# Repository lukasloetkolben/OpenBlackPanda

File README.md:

# Open Source BlackPanda for Openpilot
__This project has moved, a current version can be found here: [OpenpilotHardware](https://github.com/lukasloetkolben/OpenpilotHardware)__

The device has been tested and works so far without problems.

If you have any questions contact me on Discord: loetkolben#2962

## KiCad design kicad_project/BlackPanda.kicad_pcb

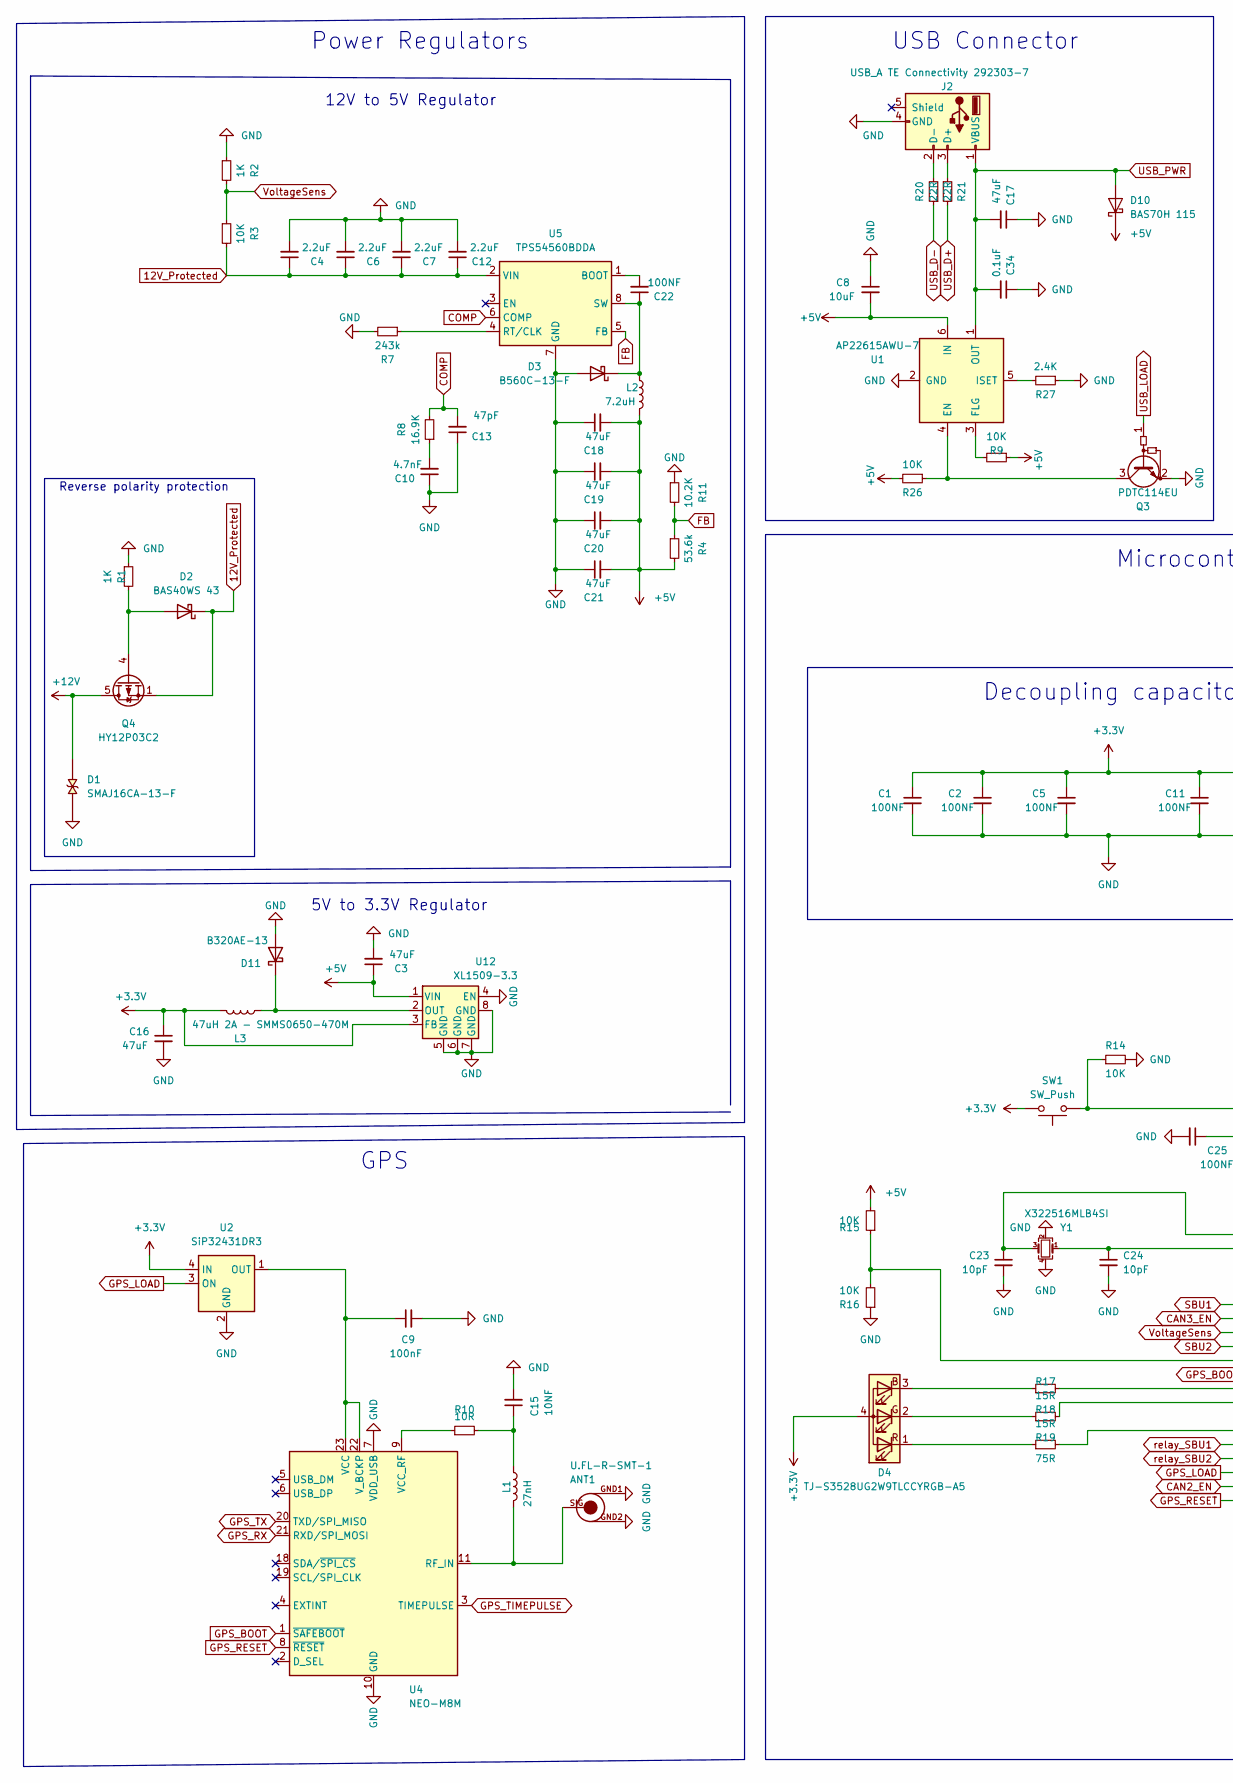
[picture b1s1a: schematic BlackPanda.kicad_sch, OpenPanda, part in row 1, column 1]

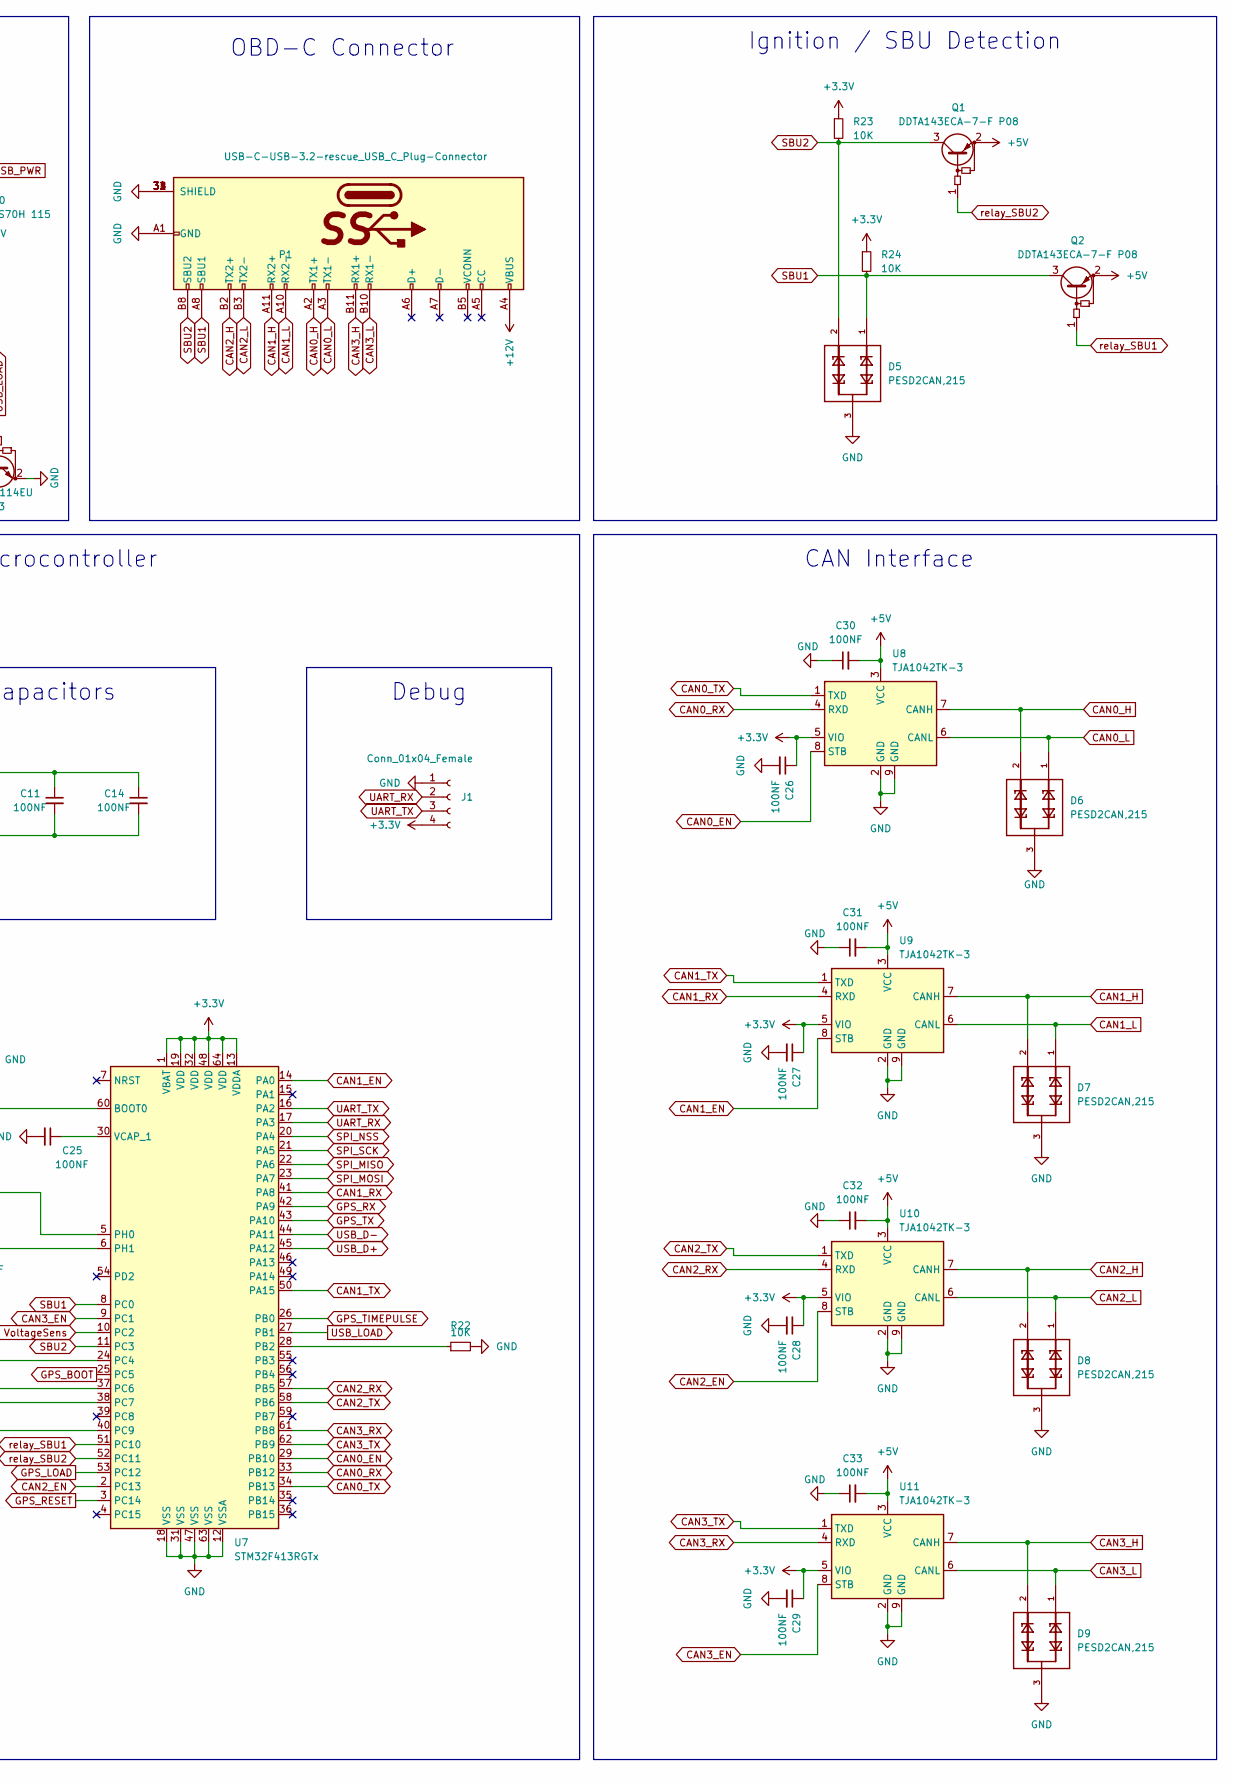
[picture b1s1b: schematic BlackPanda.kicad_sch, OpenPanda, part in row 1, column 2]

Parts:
ANT1: U.FL-R-SMT-1; PARTNUMBER U.FL-R-SMT(10)
C1, C2, C5, C11, C14, C22, C25, C26, C27, C28, C29, C30, C31, C32, C33: 100NF; C_0402_1005Metric
C3, C16, C17, C18, C19, C20, C21: 47uF; C_0805_2012Metric
C4, C6, C7, C12: 2.2uF; C_0805_2012Metric
C8: 10uF; C_0402_1005Metric
C9: 100nF; C_0603_1608Metric
C10: 4.7nF; C_0402_1005Metric
C13: 47pF; C_0603_1608Metric
C15: 10NF; C_0402_1005Metric
C23, C24: 10pF; C_0402_1005Metric
C34: 0.1uF; C_0402_1005Metric
D1: SMAJ16CA-13-F; DIOM4325X250N; PARTREV S2102
D2: BAS40WS 43; D_SOD-323
D3: B560C-13-F; D_SMC
D4: TJ-S3528UG2W9TLCCYRGB-A5; TOGIALED-TJ-S3528UG2W9TLCCYRGB
D5, D6, D7, D8, D9: PESD2CAN,215; SOT95P230X110-3N
D10: BAS70H 115; D_SOD-123F
D11: B320AE-13; D_SMA
J1: Conn_01x04_Female; PinHeader_1x04_P1.00mm_Vertical_SMD_Pin1Left
J2: USB_A TE Connectivity 292303-7; USB_A_TE_292303-7_Horizontal
L1: 27nH; L_0603_1608Metric
L2: 7.2uH; L_Wuerth_WE-PDF
L3: 47uH 2A - SMMS0650-470M; L_6.6x7.0_H4.8; JLCPCB C149588
P1: USB-C-USB-3.2-rescue_USB_C_Plug-Connector; TYPE-C-31-M-04
Q1, Q2: DDTA143ECA-7-F P08; SOT23-3
Q3: PDTC114EU; SOT-323_SC-70
Q4: HY12P03C2; PowerPAK_SO-8_Single
R1, R2: 1K; R_0402_1005Metric
R3, R9, R14, R15, R16, R22, R23, R24, R26: 10K; R_0402_1005Metric
R4: 53.6k; R_0603_1608Metric
R7: 243k; R_0402_1005Metric
R8: 16.9K; R_0402_1005Metric
R10: 10R; R_0402_1005Metric
R11: 10.2K; R_0402_1005Metric
R17, R18: 15R; R_0402_1005Metric
R19: 75R; R_0402_1005Metric
R20, R21: 22R; R_0402_1005Metric
R27: 2.4K; R_0402_1005Metric
SW1: SW_Push; SW_SPST_SKQG_WithStem
U1: AP22615AWU-7; SOT-23-6
U2: SiP32431DR3; SOT-363_SC-70-6
U4: NEO-M8M; ublox_NEO
U5: TPS54560BDDA; Texas_R-PDSO-G8_EP2.95x4.9mm_Mask2.4x3.1mm_ThermalVias
U7: STM32F413RGTx; LQFP-64_10x10mm_P0.5mm
U8, U9, U10, U11: TJA1042TK-3; DFN-8-1EP_3x3mm_P0.65mm_EP1.55x2.4mm
U12: XL1509-3.3; Diodes_PSOP-8
Y1: X322516MLB4SI; Crystal_SMD_3225-4Pin_3.2x2.5mm

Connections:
12V_Protected: C4.1, C6.1, C7.1, C12.1, D2.1 (K), Q4.1 (S), Q4.2 (S), Q4.3 (S), R3.2, U5.2 (VIN)
+3V3: C1.1, C2.1, C5.1, C11.1, C14.1, C16.1, C26.1, C27.1, C28.1, C29.1, D4.4 (A), J1.4, L3.2, R23.1, R24.1, SW1.2, U2.4 (IN), U7.1 (VBAT), U7.13 (VDDA), U7.19 (VDD), U7.32 (VDD), U7.48 (VDD), U7.64 (VDD), U8.5 (VIO), U9.5 (VIO), U10.5 (VIO), U11.5 (VIO), U12.3 (FB)
+5V: C3.1, C8.2, C18.2, C19.2, C20.2, C21.2, C30.2, C31.2, C32.2, C33.2, D10.1 (K), L2.2, Q1.2 (E), Q2.2 (E), R4.2, R9.1, R15.2, R26.2, U1.6 (IN), U8.3 (VCC), U9.3 (VCC), U10.3 (VCC), U11.3 (VCC), U12.1 (VIN)
+12V: D1.2, P1.A4 (VBUS), P1.A9 (VBUS), P1.B4 (VBUS), P1.B9 (VBUS), Q4.5 (D)
CAN0_EN: U7.29 (PB10), U8.8 (STB)
CAN0_H: D6.2, P1.A2 (TX1+), U8.7 (CANH)
CAN0_L: D6.1, P1.A3 (TX1-), U8.6 (CANL)
CAN0_RX: U7.33 (PB12), U8.4 (RXD)
CAN0_TX: U7.34 (PB13), U8.1 (TXD)
CAN1_EN: U7.14 (PA0), U9.8 (STB)
CAN1_H: D7.2, P1.A11 (RX2+), U9.7 (CANH)
CAN1_L: D7.1, P1.A10 (RX2-), U9.6 (CANL)
CAN1_RX: U7.41 (PA8), U9.4 (RXD)
CAN1_TX: U7.50 (PA15), U9.1 (TXD)
CAN2_EN: U7.2 (PC13), U10.8 (STB)
CAN2_H: D8.2, P1.B2 (TX2+), U10.7 (CANH)
CAN2_L: D8.1, P1.B3 (TX2-), U10.6 (CANL)
CAN2_RX: U7.57 (PB5), U10.4 (RXD)
CAN2_TX: U7.58 (PB6), U10.1 (TXD)
CAN3_EN: U7.9 (PC1), U11.8 (STB)
CAN3_H: D9.2, P1.B11 (RX1+), U11.7 (CANH)
CAN3_L: D9.1, P1.B10 (RX1-), U11.6 (CANL)
CAN3_RX: U7.61 (PB8), U11.4 (RXD)
CAN3_TX: U7.62 (PB9), U11.1 (TXD)
COMP: C13.2, R8.2, U5.6 (COMP)
FB: R4.1, R11.2, U5.5 (FB)
GND: ANT1.GND1, ANT1.GND2, C1.2, C2.2, C3.2, C4.2, C5.2, C6.2, C7.2, C8.1, C9.2, C10.1, C11.2, C12.2, C13.1, C14.2, C15.2, C16.2, C17.1, C18.1, C19.1, C20.1, C21.1, C23.2, C24.2, C25.2, C26.2, C27.2, C28.2, C29.2, C30.1, C31.1, C32.1, C33.1, C34.1, D1.1, D3.2 (A), D5.3, D6.3, D7.3, D8.3, D9.3, D11.2 (A), J1.1, J2.4 (GND), P1.31 (SHIELD), P1.32 (SHIELD), P1.33 (SHIELD), P1.34 (SHIELD), P1.A1 (GND), P1.A12 (GND), P1.B1 (GND), P1.B12 (GND), Q3.2 (E), R1.1, R2.1, R7.2, R11.1, R14.2, R16.1, R22.2, R27.1, U1.2 (GND), U2.2 (GND), U2.5 (GND), U4.7 (VDD_USB), U4.10 (GND), U4.12 (GND), U4.13 (GND), U4.24 (GND), U5.7 (GND), U5.9 (GND), U7.12 (VSSA), U7.18 (VSS), U7.31 (VSS), U7.47 (VSS), U7.63 (VSS), U8.2 (GND), U8.9 (GND), U9.2 (GND), U9.9 (GND), U10.2 (GND), U10.9 (GND), U11.2 (GND), U11.9 (GND), U12.4 (EN), U12.5 (GND), U12.6 (GND), U12.7 (GND), U12.8 (GND), Y1.2, Y1.4
GPS_BOOT: U4.1 (~SAFEBOOT), U7.25 (PC5)
GPS_LOAD: U2.3 (ON), U7.53 (PC12)
GPS_RESET: U4.8 (~RESET), U7.3 (PC14)
GPS_RX: U4.21 (RXD/SPI_MOSI), U7.42 (PA9)
GPS_TIMEPULSE: U4.3 (TIMEPULSE), U7.26 (PB0)
GPS_TX: U4.20 (TXD/SPI_MISO), U7.43 (PA10)
unnamed: ANT1.SIG, L1.2, U4.11 (RF_IN)
unnamed: C9.1, U2.1 (OUT), U4.22 (V_BCKP), U4.23 (VCC)
unnamed: C10.2, R8.1
unnamed: C15.1, L1.1, R10.2
unnamed: C22.1, D3.1 (K), L2.1, U5.8 (SW)
unnamed: C22.2, U5.1 (BOOT)
unnamed: C23.1, U7.5 (PH0), Y1.3
unnamed: C24.1, U7.6 (PH1), Y1.1
unnamed: C25.1, U7.30 (VCAP_1)
unnamed: D2.2 (A), Q4.4 (G), R1.2
unnamed: D4.1 (RK), R19.1
unnamed: D4.2 (GK), R18.1
unnamed: D4.3 (BK), R17.1
unnamed: D11.1 (K), L3.1, U12.2 (OUT)
unnamed: J2.2 (D-), R20.2
unnamed: J2.3 (D+), R21.1
unnamed: Q3.3 (C), R26.1, U1.4 (EN)
unnamed: R7.1, U5.4 (RT/CLK)
unnamed: R9.2, U1.3 (FLG)
unnamed: R10.1, U4.9 (VCC_RF)
unnamed: R14.1, SW1.1, U7.60 (BOOT0)
unnamed: R15.1, R16.2, U7.24 (PC4)
unnamed: R17.2, U7.37 (PC6)
unnamed: R18.2, U7.38 (PC7)
unnamed: R19.2, U7.40 (PC9)
unnamed: R22.1, U7.28 (PB2)
unnamed: R27.2, U1.5 (ISET)
SBU1: D5.1, P1.A8 (SBU1), Q2.3 (C), R24.2, U7.8 (PC0)
SBU2: D5.2, P1.B8 (SBU2), Q1.3 (C), R23.2, U7.11 (PC3)
SPI_MISO: U7.22 (PA6)
SPI_MOSI: U7.23 (PA7)
SPI_NSS: U7.20 (PA4)
SPI_SCK: U7.21 (PA5)
UART_RX: J1.2, U7.17 (PA3)
UART_TX: J1.3, U7.16 (PA2)
USB_D+: R21.2, U7.45 (PA12)
USB_D-: R20.1, U7.44 (PA11)
USB_LOAD: Q3.1 (B), U7.27 (PB1)
USB_PWR: C17.2, C34.2, D10.2 (A), J2.1 (VBUS), U1.1 (OUT)
VoltageSens: R2.2, R3.1, U7.10 (PC2)
relay_SBU1: Q2.1 (B), U7.51 (PC10)
relay_SBU2: Q1.1 (B), U7.52 (PC11)

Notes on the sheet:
USB Connector
CAN Interface
5V to 3.3V Regulator
OBD-C Connector
Decoupling capacitors
Debug
Power Regulators
12V to 5V Regulator
Microcontroller
GPS
Ignition / SBU Detection
Reverse polarity protection

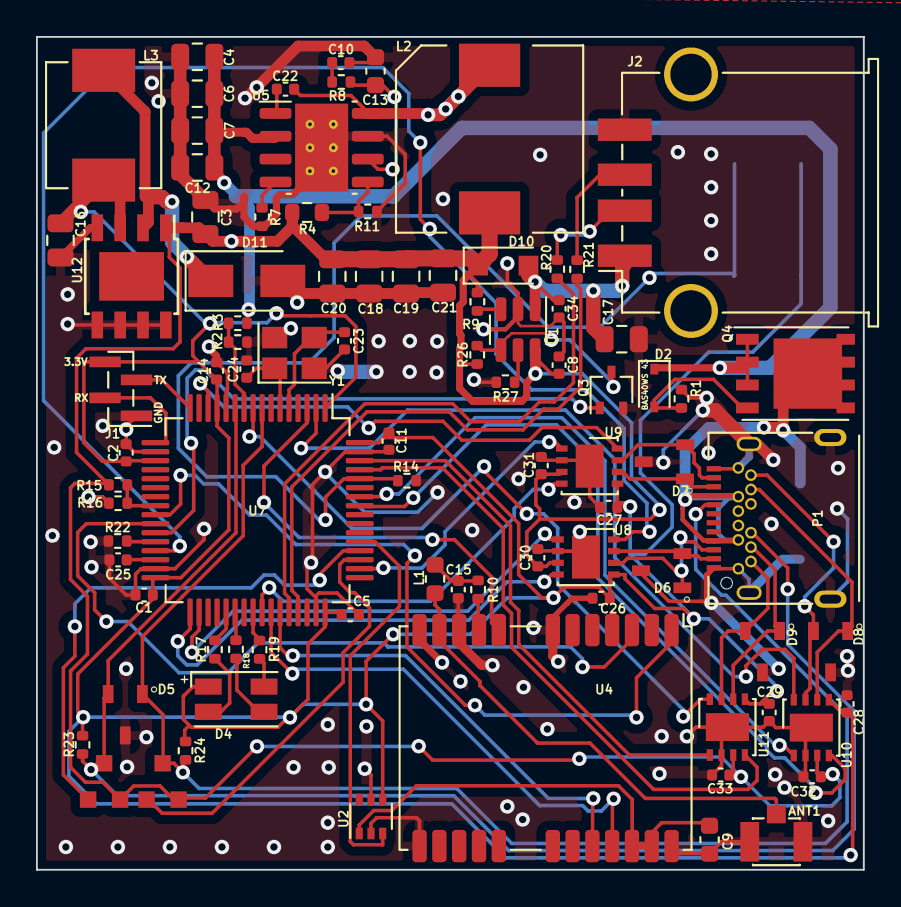
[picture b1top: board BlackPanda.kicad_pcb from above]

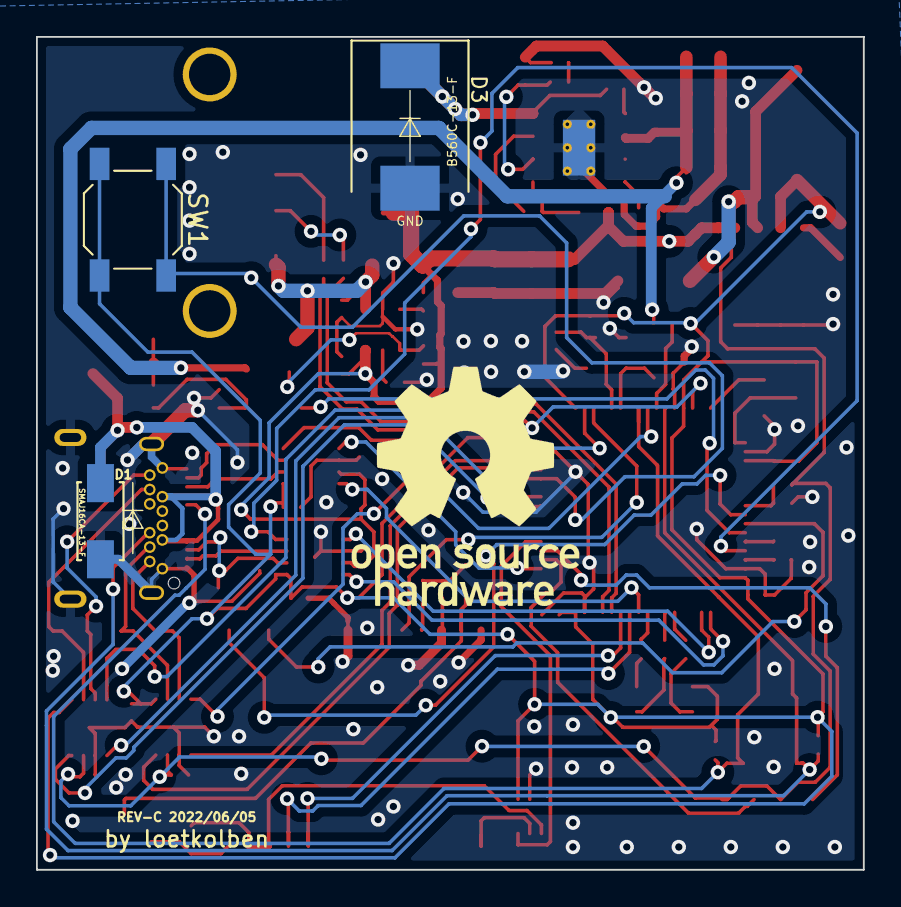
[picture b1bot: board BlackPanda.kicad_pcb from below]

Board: 2 copper layers, 45.9 x 46.3 mm, 90 parts (3 on the bottom side), 71 nets.

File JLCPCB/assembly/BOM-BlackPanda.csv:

Comment,Designator,Footprint,LCSC
100NF,C8,C_0402_1005Metric,
100NF,C14,C_0402_1005Metric,
XL1509-3.3,U12,Diodes_PSOP-8,
"PESD2CAN,215",D7,SOT95P230X110-3N,
10K,R23,R_0402_1005Metric,
10K,R24,R_0402_1005Metric,
442K,R5,R_0402_1005Metric,
19.1K,R26,R_0402_1005Metric,
4.64K,R4,R_0603_1608Metric,
10.2K,R11,R_0402_1005Metric,
2.2uF,C7,C_0805_2012Metric,
1K,R2,R_0402_1005Metric,
TPS54560BDDA,U5,Texas_R-PDSO-G8_EP2.95x4.9mm_Mask2.4x3.1mm_ThermalVias,
100NF,C25,C_0402_1005Metric,
10K,R16,R_0402_1005Metric,
100NF,C28,C_0402_1005Metric,
TJA1042TK-3,U9,DFN-8-1EP_3x3mm_P0.65mm_EP1.55x2.4mm,
PDTC114EU,Q3,SOT-323_SC-70,
U.FL-R-SMT-1,ANT1,U.FL-R-SMT-1,
75R,R19,R_0402_1005Metric,
10pF,C23,C_0402_1005Metric,
243k,R7,R_0402_1005Metric,
2.2uF,C12,C_0805_2012Metric,
100NF,C27,C_0402_1005Metric,
100NF,C11,C_0402_1005Metric,
TJA1042TK-3,U8,DFN-8-1EP_3x3mm_P0.65mm_EP1.55x2.4mm,
47uF,C20,C_0805_2012Metric,
100NF,C29,C_0402_1005Metric,
USB-C-USB-3.2-rescue_USB_C_Plug-Connector,P1,TYPE-C-31-M-04,
47uF,C3,C_0805_2012Metric,
10pF,C24,C_0402_1005Metric,
15R,R18,R_0402_1005Metric,
7.2uH,L2,L_Wuerth_WE-PDF,
47uF,C21,C_0805_2012Metric,
100NF,C30,C_0402_1005Metric,
"PESD2CAN,215",D9,SOT95P230X110-3N,
Conn_01x04_Female,J1,PinHeader_1x04_P1.00mm_Vertical_SMD_Pin1Left,
DDTA143ECA-7-F P08,Q1,SOT23-3,
SiP32431DR3,U2,SOT-363_SC-70-6,
100NF,C32,C_0402_1005Metric,
47uF,C19,C_0805_2012Metric,
"PESD2CAN,215",D5,SOT95P230X110-3N,
470NH,L1,L_0603_1608Metric,
15R,R17,R_0402_1005Metric,
2.2uF,C6,C_0805_2012Metric,
"PESD2CAN,215",D6,SOT95P230X110-3N,
TPS2549IRTETQ1,U6,WQFN-16-1EP_3x3mm_P0.5mm_EP1.75x1.75mm,
DDTA143ECA-7-F P08,Q2,SOT23-3,
TJ-S3528UG2W9TLCCYRGB-A5,D4,TOGIALED-TJ-S3528UG2W9TLCCYRGB,
47pF,C13,C_0603_1608Metric,
22R,R21,R_0402_1005Metric,
10K,R27,R_0402_1005Metric,
100NF,C15,C_0402_1005Metric,
USB_A TE Connectivity 292303-7 ,J2,USB_A_TE_292303-7_Horizontal,
100nF,C9,C_0603_1608Metric,
"PESD2CAN,215",D8,SOT95P230X110-3N,
4.7nF,C10,C_0402_1005Metric,
STM32F413RGTx,U7,LQFP-64_10x10mm_P0.5mm,
100NF,C1,C_0402_1005Metric,
NEO-M8M,U4,ublox_NEO,
100NF,C31,C_0402_1005Metric,
16.9K,R8,R_0402_1005Metric,
BAS40WS 43 ,D2,D_SOD-323,
TJA1042TK-3,U10,DFN-8-1EP_3x3mm_P0.65mm_EP1.55x2.4mm,
47uF,C18,C_0805_2012Metric,
47uF,C16,C_0805_2012Metric,
10K,R13,R_0402_1005Metric,
TJA1042TK-3,U11,DFN-8-1EP_3x3mm_P0.65mm_EP1.55x2.4mm,
10K,R15,R_0402_1005Metric,
1K,R1,R_0402_1005Metric,
10K,R22,R_0402_1005Metric,
22R,R20,R_0402_1005Metric,
100NF,C2,C_0402_1005Metric,
48.7K,R12,R_0603_1608Metric,
100NF,C5,C_0402_1005Metric,
100NF,C26,C_0402_1005Metric,
2.2uF,C4,C_0805_2012Metric,
100NF,C33,C_0402_1005Metric,
10R,R10,R_0402_1005Metric,
10K,R14,R_0402_1005Metric,
10K,R3,R_0402_1005Metric,
90.9R,R6,R_0402_1005Metric,
SIS427EDN-T1-GE3,U1,SIS427EDN-T1-GE3,
X322516MLB4SI,Y1,Crystal_SMD_3225-4Pin_3.2x2.5mm,
B320AE-13,D11,D_SMA,
BAS70H 115,D10,D_SOD-123F,
100NF,C22,C_0402_1005Metric,
47uH 2A - SMMS0650-470M,L3,L_6.6x7.0_H4.8,
SW_Push,SW1,SW_SPST_SKQG_WithStem,
B560C-13-F,D3,D_SMC,
SMAJ16CA-13-F,D1,DIOM4325X250N,

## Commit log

2022-06-06 initial
2022-06-06 Schematics PDF
2022-06-06 LICENSE
2022-06-06 added picture
2022-06-30 inductor
2022-07-01 readme
2022-11-28 Capacitor incorrect value.
2023-06-21 OpenpilotHardware
